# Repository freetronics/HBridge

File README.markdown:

Freetronics H-Bridge Shield
===========================
Copyright 2014 Freetronics Pty Ltd  
Freetronics site:  www.freetronics.com  
Freetronics email: info@freetronics.com  

FIXME

Features:

 * Overlay guide where you need it (both top and bottom)
 * FIXME

You can view more at our product page at:

  http://www.freetronics.com/hbridge

The "docs" folder within this repository includes a handy copy of the
schematic in PDF format, images of the pcb, and our Getting Started
guide that ships with each board.

INSTALLATION
------------
The design is saved as an EAGLE project. EAGLE PCB design software is
available from www.cadsoftusa.com free for non-commercial use. To use
this project download it and place the directory containing these files
into the "eagle" directory on your computer. Then open EAGLE and
navigate to Projects -> eagle -> HBridge.

DISTRIBUTION
------------
The specific terms of distribution of this project are governed by the
license referenced below.

LICENSE
-------
Licensed under the TAPR Open Hardware License (www.tapr.org/OHL).
The "license" folder within this repository also contains a copy of
this license in plain text format.

CREDITS
-------
The H-Bridge Shield was designed by Luke Weston (reindeerflotilla@gmail.com)

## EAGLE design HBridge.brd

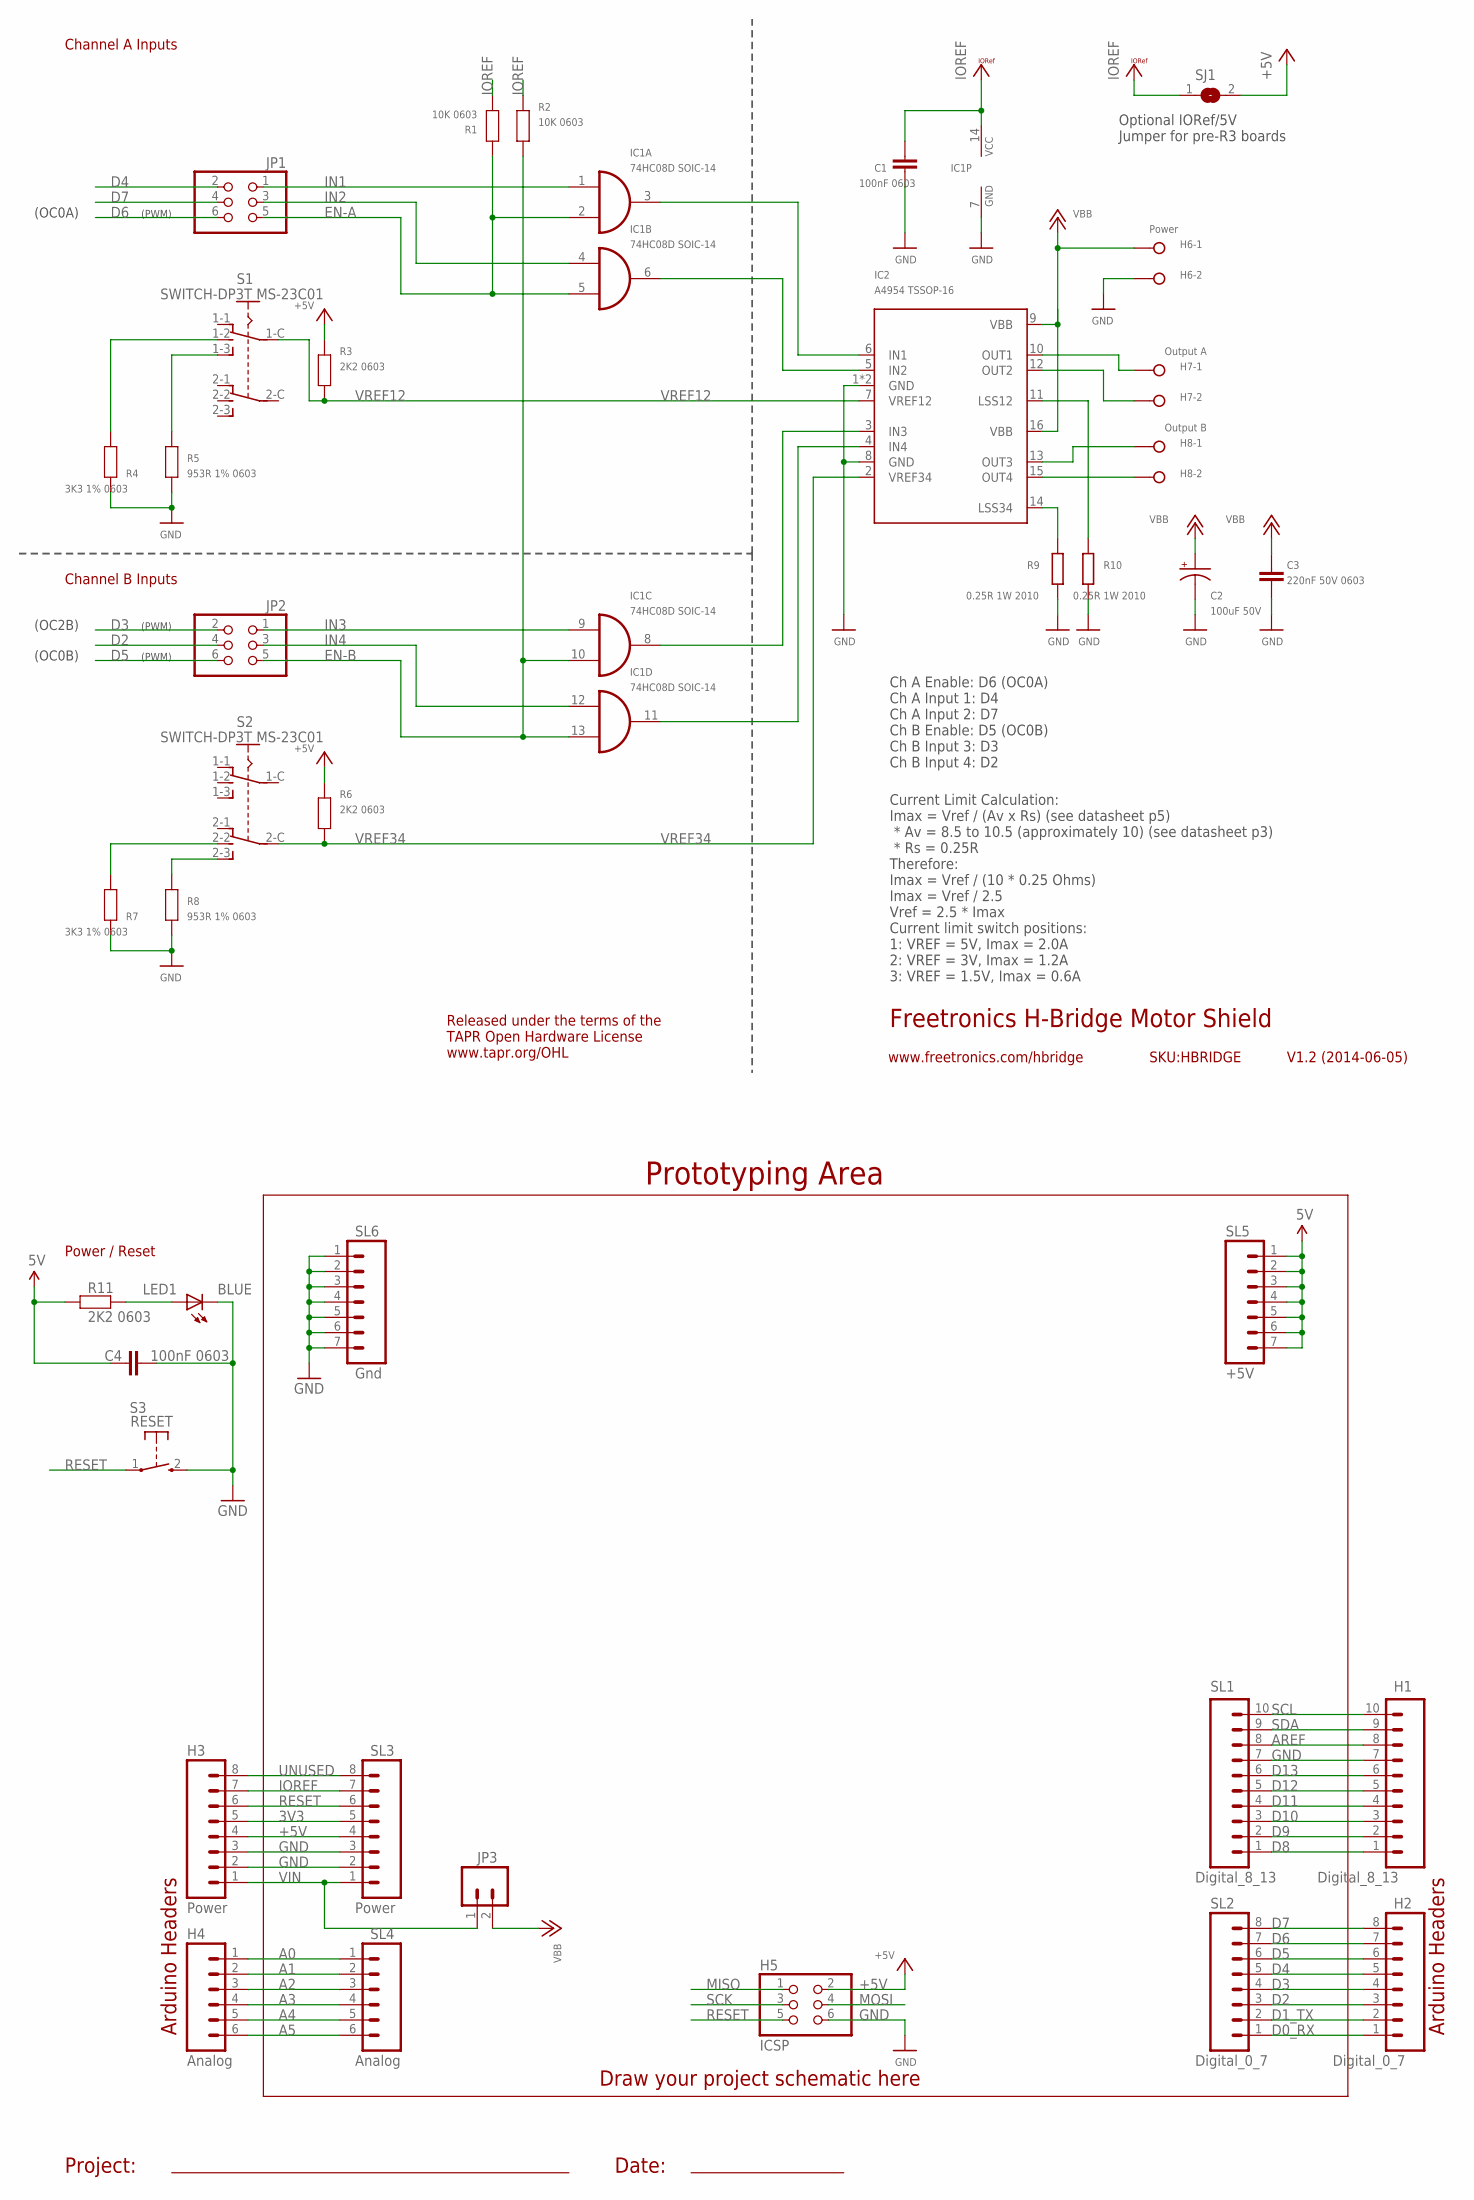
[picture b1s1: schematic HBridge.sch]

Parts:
C1, C4: 100nF 0603; 0603
C2: 100uF 50V; PANASONIC_E
C3: 220nF 50V 0603; 0603
H1: Digital_8_13; 1X10
H2: Digital_0_7; 1X08
H3: Power; 1X08
H4: Analog; 1X06
H5: ICSP; 2X03
H6: Power; W237-132
H7: Output A; W237-132
H8: Output B; W237-132
IC1: 74HC08D SOIC-14; SO14
IC2: A4954 TSSOP-16; TSSOP16-LP
JP1, JP2: PINHD-2X3; 2X03
JP3: M02PTH; 1X02
LED1: BLUE; LED-0603
R1, R2: 10K 0603; 0603
R3, R6, R11: 2K2 0603; 0603
R4, R7: 3K3 1% 0603; 0603
R5, R8: 953R 1% 0603; 0603
R9, R10: 0.25R 1W 2010; R2010
S1, S2: SWITCH-DP3T MS-23C01; MS-23C01
S3: RESET; TACTILE_SWITCH_SMD_2PIN_TINY
SJ1: SJ
SL1: Digital_8_13; 1X10
SL2: Digital_0_7; 1X08
SL3: Power; 1X08
SL4: Analog; 1X06
SL5: +5V; 1X07
SL6: Gnd; 1X07

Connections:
3V3: H3.5, SL3.5
+5V: C4.1, H3.4, H5.2, R3.1, R6.1, R11.1, SJ1.2, SL3.4, SL5.1, SL5.2, SL5.3, SL5.4, SL5.5, SL5.6, SL5.7
A0: H4.1, SL4.1
A1: H4.2, SL4.2
A2: H4.3, SL4.3
A3: H4.4, SL4.4
A4: H4.5, SL4.5
A5: H4.6, SL4.6
AREF: H1.8, SL1.8
D0_RX: H2.1, SL2.1
D1_TX: H2.2, SL2.2
D2: H2.3, JP2.4, SL2.3
D3: H2.4, JP2.2, SL2.4
D4: H2.5, JP1.2, SL2.5
D5: H2.6, JP2.6, SL2.6
D6: H2.7, JP1.6, SL2.7
D7: H2.8, JP1.4, SL2.8
D8: H1.1, SL1.1
D9: H1.2, SL1.2
D10: H1.3, SL1.3
D11: H1.4, SL1.4
D12: H1.5, SL1.5
D13: H1.6, SL1.6
EN-A: IC1.2 (I1), IC1.5 (I1), JP1.5, R1.2
EN-B: IC1.10 (I1), IC1.13 (I1), JP2.5, R2.1
GND: C1.2, C2.-, C3.2, C4.2, H1.7, H3.2, H3.3, H5.6, H6.2, IC1.7 (GND), IC2.1 (GND), IC2.8 (GND), IC2.EXP (GND), LED1.C, R4.2, R5.2, R7.2, R8.2, R9.1, R10.1, S3.2 (S), SL1.7, SL3.2, SL3.3, SL6.1, SL6.2, SL6.3, SL6.4, SL6.5, SL6.6, SL6.7
IN1: IC1.1 (I0), JP1.1
IN2: IC1.4 (I0), JP1.3
IN3: IC1.9 (I0), JP2.1
IN4: IC1.12 (I0), JP2.3
IOREF: C1.1, H3.7, IC1.14 (VCC), R1.1, R2.2, SJ1.1, SL3.7
MISO: H5.1
MOSI: H5.4
unnamed: R8.1, S2.2-3
unnamed: IC1.11 (O), IC2.4 (IN4)
unnamed: IC1.8 (O), IC2.3 (IN3)
unnamed: IC1.6 (O), IC2.5 (IN2)
unnamed: IC1.3 (O), IC2.6 (IN1)
unnamed: H7.1, IC2.10 (OUT1)
unnamed: H7.2, IC2.12 (OUT2)
unnamed: H8.1, IC2.13 (OUT3)
unnamed: H8.2, IC2.15 (OUT4)
unnamed: IC2.14 (LSS34), R9.2
unnamed: IC2.11 (LSS12), R10.2
unnamed: R4.1, S1.1-2
unnamed: R5.1, S1.1-3
unnamed: LED1.A, R11.2
unnamed: R7.1, S2.2-2
RESET: H3.6, H5.5, S3.1, SL3.6
SCK: H5.3
SCL: H1.10, SL1.10
SDA: H1.9, SL1.9
UNUSED: H3.8, SL3.8
VBB: C2.+, C3.1, H6.1, IC2.9 (VBB), IC2.16 (VBB), JP3.2
VIN: H3.1, JP3.1, SL3.1
VREF12: IC2.7 (VREF12), R3.2, S1.1-C
VREF34: IC2.2 (VREF34), R6.2, S2.2-C

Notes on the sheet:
Prototyping Area
Power / Reset
Arduino Headers
Draw your project schematic here
Project:
Date:
Freetronics H-Bridge Motor Shield
V1.2 (2014-06-05)
www.freetronics.com/hbridge
SKU:HBRIDGE
Current Limit Calculation: Imax = Vref / (Av x Rs) (see datasheet p5) * Av = 8.5 to 10.5 (approximately 10) (see datasheet p3) * Rs = 0.25R Therefore: Imax = Vref / (10 * 0.25 Ohms) Imax = Vref / 2.5 Vref = 2.5 * Imax Current limit switch positions: 1: VREF = 5V, Imax = 2.0A 2: VREF = 3V, Imax = 1.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
Channel A Inputs
Channel B Inputs
(PWM)
(OC0B)
Released under the terms of the TAPR Open Hardware License www.tapr.org/OHL
(OC2B)
(OC0A)
Ch A Enable: D6 (OC0A) Ch A Input 1: D4 Ch A Input 2: D7 Ch B Enable: D5 (OC0B) Ch B Input 3: D3 Ch B Input 4: D2
Optional IORef/5V Jumper for pre-R3 boards

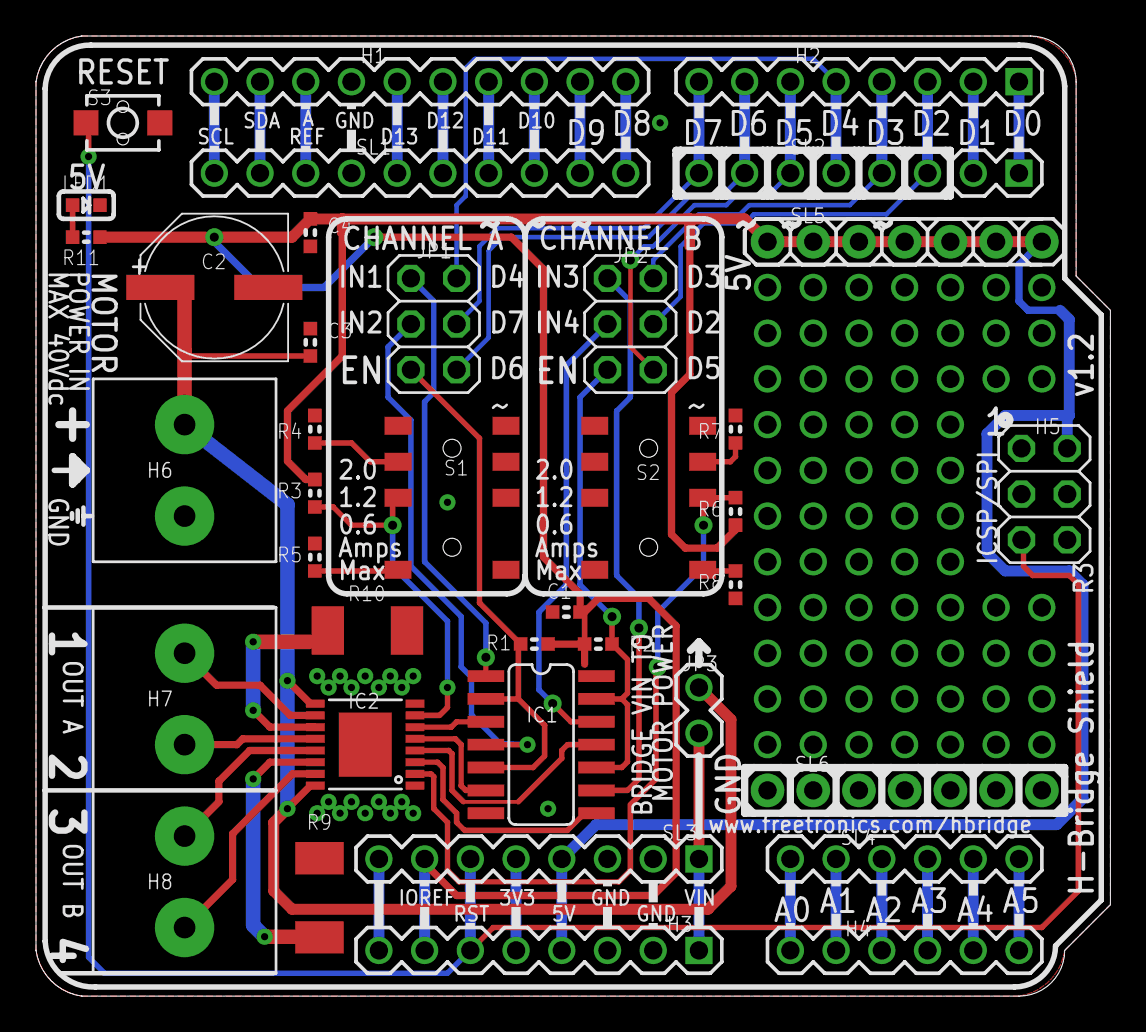
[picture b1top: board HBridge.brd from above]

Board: 2 copper layers, 59.7 x 53.3 mm, 39 parts (1 on the bottom side), 54 nets.

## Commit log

2012-11-04 Added ICSP header for R3
2012-11-04 Replaced reset button with smaller 2-pin version
2012-11-04 Restructured docs
2012-11-04 Removed obsolete gerbers
2012-11-04 Fixed contributors
2012-11-04 Improved position of pwr LED
2012-11-05 Made track widths consistent; renamed parts; relocated designators, improved silkscreen
2012-11-05 Ground polygon tweak
2013-03-31 Restructured schematic and board for switchable current limit
2013-04-03 Changed input pins; rerouted; ERC and DRC
2013-07-18 Annotation updates for release
2014-06-04 Add schematic PDF
2014-06-05 Version 1.2: 3.3V compatibility via the IORef pin on Arduino R3
2014-06-05 add a gitignore
2014-06-30 Remove second version number and update first V1.2, bump Copyright date
2018-03-28 Fixed date

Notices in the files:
HBridge.brd:
(c) 2014 Freetronics Pty Ltd
parts and their libraries:
freetronics-original: Licensing: CC v3.0 Share-Alike You are welcome to use this library for commercial purposes.
